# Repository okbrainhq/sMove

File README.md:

# sMove — PCB + three-piece enclosure

> **Schematic ECO 2026-09-15 (SCHEMATIC ONLY — no PCB change, no routing).** Added **SW1**, an off-board pack toggle switch in series in the battery + lead (hard "True OFF", ≥0.5 A / <50 mΩ, wired to the same 2.54 mm wire-pad footprint as J2); routed the charger's open-drain **CHG_N** to **U1 GPIO6** with a 100k pull-up (**R24**); and changed **U4** to **XC6220B331MR-G** (SOT-25, LCSC C86534) with a new footprint `SOT-25_XC6220`. The AP2112K's SOT-23-5 pin map is identical (1=VIN 2=VSS 3=CE 4=NC 5=VOUT), so no rewire was needed. ERC is **0 violations**, matching the pre-change baseline; the board, `dist/` and enclosure data are unchanged and stale until a forward update (F8) plus placement is done. See [Main PCB status](PCB/main/README.md) and [radio/battery architecture](docs/revision-r2/integrated/RADIO-BATTERY.md).

> **Current PCB workspace revision: components staged, UNROUTED.** [Main PCB status](PCB/main/README.md): schematic links repaired; ESP32/U1, USB-C/J1, IMU/U2 and battery +/− holes/J2 remain fixed, with the other 43 footprints staged to the right for manual placement. No tracks/vias; latest zone state preserved. Forward schematic update reports 0 errors/warnings and DRC finds 0 schematic-parity issues. A pre-existing J2/U1 courtyard overlap and unrouted connections remain. **Not for fabrication or charging; exports/enclosure data are stale.**

> **Historical routed PCB revision:** [Routing completion, plane selection and verification](docs/revision-r2/main-routing/README.md): the user's rotated-U8 USB layout is retained, remaining nets use top/bottom routing, In1 is GND and In2 contains power regions. **0 DRC errors, 0 unconnected items, 0 parity issues; one existing J2 library warning.** [Reusable routing/rotation tools](scripts/pcb_tools/README.md) include exact manual coordinates and vias. **Not a fabrication/charging release; `dist/` and enclosure exports remain stale.** Earlier enclosure descriptions below are historical. The prior RED LED GPIO3 change remains required.

> **Previous PCB update:** The [LED is now fully routed on the user's revised layout](docs/revision-r2/led-routing/README.md), with top-left/bottom-right space reserved for future M3 hardware. The enclosure and `PCB/main/dist/` remain older snapshots; their alignment/manufacturing claims below do not apply to the revised PCB without regeneration and review.

**Current review: white rounded Midframe + Top cover + Bottom cover. No screws, nuts, inserts or PCB enclosure-mounting holes. Default outer wall 0.8 mm; configurable and checked at 1.2 mm. No merge, manufacturing release or charging release.**

- [Current enclosure and regeneration](housing/README.md): opposite-side battery/PCB pockets, insulated support, optional PCB adhesive, screwless sleeve/snap covers and an internal perimeter BAT route around the separator edge.
- [PCB](PCB/main/README.md): targeted H1/keepout removal and copper refill; all 1,726 tracks and 97 vias preserved. Circuit, pad geometry, aligned buttons, antenna rules and battery interface unchanged.
- [JLCPCB fabrication/assembly export](scripts/jlcpcb/README.md): regenerates `PCB/main/dist/jlcpcb/` (`gerber.zip`, `bom.csv`, `pick_and_place.csv`, `export-report.json`) from the native KiCad `LCSC`/`MPN` fields on the symbols and footprints.
- [Historical screwless revision evidence](docs/revision-r2/screwless/README.md): fresh configured DRC/ERC, full native comparisons, manifold solids, collision/access checks, actual wall variation, FreeCAD images and hash manifests.
- [Printing/assembly and physical gates](housing/PRINTING-ASSEMBLY.md): actual pack/lead exit, insulation/adhesive, print supports, snap fit/creep, PCB deflection and charging qualification still required. No proven physical fit.

Default envelope including snap reinforcement: **42.85 L × 34.3 W × 19.0 H mm**. Accepted 30×20×3 mm battery candidate / 31×21×4.3 mm complete-pack allowance retained, behind the north antenna exclusion. Main underside faces the body; IMU +Z remains outward. LED, RESET/BOOT and USB-C accesses align to the current native PCB.

Previous [button alignment](docs/revision-r2/button-alignment/README.md), [PCB repair](docs/revision-r2/pcb-repair/README.md), and [two-part case](docs/revision-r2/two-part-case/README.md) records are historical snapshots, not current assembly instructions. Unrelated electronics and history are preserved.

### Enclosure-only RF test prototype

Current `housing/` preserves the validated 25×30 mm PCB unchanged. Three screwless prints integrate a protected original-module antenna cap, source-derived flush USB mouth and internal perimeter BAT route around (not through) the separator. Overall 42.85×34.3×19.0 mm at 0.8 mm walls. See [housing documentation](housing/README.md) for source evidence, nominal checks and physical/RF/sweat qualification holds. No PCB shrinking or external antenna substitution.

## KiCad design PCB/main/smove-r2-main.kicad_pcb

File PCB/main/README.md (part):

# Main PCB — 25 × 30 × 1 mm manual-layout reset

## Current schematic ECO — pack cutoff switch, charger status, 3V3 LDO (2026-09-15, SCHEMATIC ONLY)

Applied to `power.kicad_sch`, `compute.kicad_sch` and `smove-r2-main.kicad_sch`:

* **SW1 — hard pack cutoff.** An off-board toggle switch in series in the battery **+** lead, upstream of the `PACK_P` node. Schematic symbol uses the same 2.54 mm two-pad wire footprint as J2 (`smove-r2-main:BatteryWire_2x_PTH_P2.54mm_D1.0mm`), `in_bom no` (user-supplied off-board part: **≥0.5 A rating, contacts <50 mΩ, ≥6 V DC**). Net split: `/Power/PACK_RAW` = J2.1 + SW1.2, `/Power/PACK_P` = SW1.1 + C2.1 + R14.1 + U6.2 + U6.3. This provides the *True OFF* that `docs/revision-r2/integrated/RADIO-BATTERY.md` records as missing.
* **R24 (100k, LCSC C25741) + `/CHG_N` net — charger status to the MCU.** Charger open-drain `CHG_N` (U6 pin 9) is pulled up to 3V3_MAIN and routed to **U1 pad 20 = GPIO6**; `/CHG_N` = U6.9 + R24.2 + U1.20. New sheet pin added to both the Power and Compute sheet symbols.
* **U4 = XC6220B331MR-G** (Torex, LCSC C86534) replaces `AP2112K-3.3TRG1`. The SOT-25 pin map **1=VIN 2=VSS 3=CE 4=NC 5=VOUT** is the *same function map* as the AP2112K SOT-23-5 it replaces, so no rewire and no pad remap was needed. New footprint `assets/smove-r2-main.pretty/SOT-25_XC6220.kicad_mod` (JEDEC MO-178 Var AA land pattern, identical geometry to `SOT-23-5`); the SW1 symbol was added to `assets/smove-r2-main.kicad_sym`.
* `J2` was moved down 10.16 mm **on the sheet only** (cosmetic, no connectivity change) to make room for SW1.

Verification (KiCad 9.0.8): `kicad-cli sch erc` reports **0 violations — identical to the HEAD baseline**, and `kicad-cli sch export netlist` confirms the three nets above.

**Deliberately not done — no PCB change and no routing.** The board still carries the AP2112K SOT-23-5 at U4 (its footprint field now differs from the schematic) and has no SW1/R24 footprints, so a forward update (F8) plus manual placement is required before parity is restored. `dist/` and the enclosure data remain stale and must be regenerated (`python3 scripts/jlcpcb/export.py PCB/main --overwrite`) after the board is updated. **Engineering prototype — no charge or fabrication approval.**

## Library and asset layout

All project-local KiCad libraries and models now live under `assets/` (moved from the project root; content byte-identical apart from the references below):

| Path | Contents |
|---|---|
| `assets/smove-r2-main.pretty/` | main footprint library (nickname `smove-r2-main`) |
| `assets/imu.pretty/` | integrated-IMU footprint library (nickname `imu`) |
| `assets/smove-r2-main.kicad_sym`, `assets/imu.kicad_sym`, `assets/Device.kicad_sym`, `assets/power.kicad_sym` | project-local symbol libraries |
| `assets/imu-models/` | local STEP models, referenced as `${KIPRJMOD}/assets/imu-models/...` |

`fp-lib-table`/`sym-lib-table` stay at the project root and point at `${KIPRJMOD}/assets/...`. Schematic sheets, project/design-rule files and `dist/` are untouched; only the U2 3D-model path (in the board and in `assets/imu.pretty/InvenSense_QFN-24_3x3mm_P0.4mm.kicad_mod`) changed text.

Verified with KiCad 9.0.8: the board reloads with the same 47 footprints, 461 tracks and 7 zones; DRC reports 0 violations / 0 unconnected / 0 schematic-parity (the DRC library check covers footprint-library resolution), ERC reports 0 violations, and all four symbol libraries parse and still contain every referenced symbol. Historical ECO scripts under `scripts/r2/` (for example `integrated/migrate.py`, `integrated/layout.py`) still name the pre-move project-root paths; they are documented as destructive historical helpers and must not be rerun on this board.

**Status note:** the headings below describe earlier working states. DRC on the currently saved `smove-r2-main.kicad_pcb` reports 0 violations, 0 unconnected items and 0 schematic-parity issues, and no footprint origin lies outside the board outline, so the "UNROUTED / components staged" wording below is stale and has not been rewritten here.

## M3 screw mounting holes with grounded copper rings (2026-09-15)

Three plated 3.2 mm M3 clearance holes were added to the three free board corners, each
with a 5.0 mm grounded copper ring on all four copper layers:

| Ref | Corner | Centre (native mm) | Hole | Ring | Net |
|---|---|---|---|---|---|
| **H1** | top-left | 103.20, 103.20 | 3.2 mm plated | 5.0 mm Ø, 0.90 mm annular, mask open | `GND` |
| **H2** | bottom-left | 103.20, 126.80 | 3.2 mm plated | same | `GND` |
| **H3** | bottom-right | 121.80, 126.80 | 3.2 mm plated | same | `GND` |

* Each centre is exactly 3.20 mm in from both adjacent edges, so the three holes are
  identical except for the corner they avoid. The top-right corner is **occupied** by J2
  and R3/R4/U8 — 1.4 mm of clear width, less than the drill.
* Footprint `smove-r2-main:MountingHole_3.2mm_M3_Pad_5mm` lives in
  `assets/smove-r2-main.pretty/`. It is a reduced-ring variant of KiCad's
  `MountingHole:MountingHole_3.2mm_M3_Pad`: that part's 6.4 mm pad needs 3.45 mm of
  board-edge clearance and does not fit any corner of this board. 5.0 mm is the largest
  ring that keeps ≥0.25 mm copper-to-edge (actual 0.70 mm), ≥0.15 mm foreign-net
  clearance (actual 0.44/1.10/0.81 mm) and a non-overlapping courtyard (actual
  0.26/0.41/0.33 mm, courtyard = the 5.5 mm M3 head envelope) at all three positions.
* `board_only`, excluded from BOM and position files, no schematic symbol: mounting
  hardware is not a purchased or placed part, and schematic parity stays 0.
* **Zones were deliberately not refilled.** The rings join the GND node by overlapping
  the saved In1.Cu plane (all three centres are inside the fill, DRC 0 unconnected). A
  fresh refill would re-cut 31.6 mm² of that plane even on the unmodified board, which
  is not part of this change.
* Board diff is **+333 lines, 0 deletions**; deleting the three footprint blocks
  reproduces the previous board byte-for-byte. `bom.csv` and `pick_and_place.csv` are
  byte-identical; the Gerbers gain only the three 5.0 mm rings and their mask openings,
  and the PTH drill gains one `T4C3.200` tool with three hits.
* DRC **0 / 0 / 0**, ERC **0**. See the
  [change record](../../docs/revision-r2/m3-mounting-holes/README.md) and its
  `verification.json`; reproduce with `python3 scripts/r2/final/m3_mounting_holes.py
  --check --geometry` and `python3 scripts/r2/m3-mounting-holes/verify.py`.
* **The enclosure does not have these holes.** `housing/` is still the screwless
  revision (no bosses, threads or inserts); it needs a companion revision before M3
  hardware is usable. Physical fit, torque and the RF effect of the new metal near the
  ESP32-C3 antenna are unqualified.

## Silkscreen outlines, pin-1 markers and free-library parts (2026-09-15)

All 46 assembled parts still carry verified `LCSC`+`MPN` fields, and the export
(`python3 scripts/jlcpcb/export.py PCB/main`) now also reflects these changes; see the
[change record](../../docs/revision-r2/silk-and-basic-parts/README.md) and its
`verification.json`, renders and live BOM audit.

* **U6** (BQ24074RGTR) had *no* silkscreen, so it had no pin-1 indicator: three corner
  brackets plus the same outside pin-1 arrowhead the IMU (U2) uses now point at the
  TS/pad-1 corner.
* **U1** (ESP32-C3-MINI-1) body outline and antenna boundary existed only on `F.Fab`.
  `F.Fab` is not part of the Gerber set, so JLCPCB's placement preview showed the module
  as bare 0.4 mm pads — that is why it "did not line up" there. The body outline is now
  copied to `F.SilkS`, clipped at the 100.0 mm board edge where the module overhangs,
  and the `F.Fab` corner chamfer is deliberately not copied (it crosses the left anchor pad).
* **J1** (USB-C receptacle) had no silkscreen at all — the standard shell lines were on
  `F.Fab` — so the same problem applied. Its shell sides and pad-side end are now on
  `F.SilkS`, offset past the `S1` shell pads and clipped at the board-edge notch.
* **D1** (LTST-C19HE1WT) got a closed silkscreen outline outside the land pattern with a
  gap over the pad-1 corner.
* The same geometry was added to the project-local library footprints
  (`assets/smove-r2-main.pretty/*.kicad_mod`), so the DRC library check stays clean.
* **C3** moved from `C29277` (22 µF 10 V, Extended, $3 setup fee) to **`C45783`
  (22 µF 25 V X5R 0805, Basic)**. Every other resistor and capacitor is already
  Basic/Preferred Extended and therefore fee-free, including R21 (`C25924`); the
  estimated extended-part fee drops from $33.00 to $30.00, and the remaining charge is
  the ten design-fixed actives.

Verification: DRC **0 violations / 0 unconnected / 0 schematic-parity**, ERC **0**, added
silk keeps ≥0.17 mm to the nearest pad (board rule 0.10 mm), `F_Silkscreen.gto` gains 36
draw commands, `bom.csv` differs only in the C3 row and `pick_and_place.csv` is
byte-identical. C45783's pocket-height check and a fresh DC-bias screen are still open.

## JLCPCB fabrication and assembly export

`/usr/bin/python3 scripts/jlcpcb/export.py PCB/main` (add `--overwrite` to refresh an existing
set) writes `dist/jlcpcb/`: `gerber.zip` (all four copper layers, masks, silkscreen, paste, edge
cuts, separate PTH/NPTH millimetre drills), `bom.csv`, `pick_and_place.csv` and
`export-report.json`. See the [export tool documentation](../../scripts/jlcpcb/README.md).

- Generated from the currently saved board (47 footprints, 461 tracks, 70 vias, 7 zones, 4 copper
  layers, aux origin 100/135) at this revision. Native DRC/parity on that same file reports
  **0 violations, 0 unconnected items, 0 schematic-parity issues**; the export tool re-verifies
  KiCad's own position output against the board file before writing anything.
- All **46** assembled parts carry a JLCPCB/LCSC catalogue number in the native `LCSC` field,
  together with `MPN`, on both the schematic symbols and the board footprints. The verified
  numbers are recorded in [main-parts.csv](../../docs/revision-r2/main-parts.csv) and
  [stock.json](../../docs/revision-r2/stock.json). J2 (the two plated battery wire holes) is
  intentionally PCB-only and excluded from both BOM and CPL.
- Engineering export only: **not a fabrication, assembly or charging release**. The tool does not
  refill zones, run DRC/ERC, check supplier stock or qualify any purchase code, and `housing/`
  remains a separate historical snapshot.

## Current: schematic links repaired; components staged — UNROUTED

**All 47 schematic footprints are now present.** U1 (ESP32), J1 (USB-C), U2 (IMU), and J2 (battery +/− holes) retain their poses and geometry. The other **43 footprints are staged outside the board to the right** for manual placement. No tracks or vias were added.

The reported dialog was **Update Schematic from PCB**, the reverse direction. Use **Tools → Update PCB from Schematic (F8)** to bring schematic components into the board. The four old footprint paths also contained an extra root-sheet UUID; one reference-based re-link repaired them without replacing or moving the footprints. Re-link is now off for normal updates. A repeat forward-update preview reports **0 errors and 0 warnings**, without duplicate additions. KiCad also repaired duplicate pad UUIDs on save; all pad geometry/nets and footprint UUIDs remain unchanged.

[Update verification](../../docs/revision-r2/manual-layout-reset/schematic-update-verification.json): **0 schematic-parity issues**, 148 expected unconnected items, and one **pre-existing J2/U1 courtyard overlap**, left unchanged to preserve both fixed positions. Schematics and design rules on disk are unchanged. The latest saved zone state was preserved: five rule areas and one filled In1 GND plane; the earlier six-unfilled-zone reset below is historical. **Not for manufacture or charging; exports remain stale.**

## Historical: manual placement/routing reset — UNROUTED

Only **U1 (ESP32), J1 (USB-C), U2 (IMU), and J2 (battery +/− through-hole pads)** remain in the PCB layout, with their complete footprint definitions, positions, orientations and pad/net assignments unchanged. The other **43 footprints were deleted from the PCB only**; all schematic sheets and project/rule files remain unchanged.

Removed **500 track segments, 124 vias, and all 38 cached copper-fill polygons**. All six copper-zone definitions are retained **unfilled**, including In1 GND and the In2 GND / 3V3_MAIN / PACK_P regions. Board outline, stackup, drawings and all keepouts are unchanged. This is actual copper removal, not merely hidden pours.

[Verification](../../docs/revision-r2/manual-layout-reset/verification.json): exact-token preservation check and native board load pass; native DRC reports **0 geometric violations**, **45 intentionally unconnected items**, and **43 expected missing-footprint parity warnings**, plus the existing J2 library-footprint mismatch warning. Previous routed-board acceptance scripts/reports below are historical and are not acceptance criteria for this reset. **Not for fabrication/assembly/charging; existing exports and enclosure placement data are stale.**

For manual placement, open `smove-r2-main.kicad_pro` in KiCad and use **Update PCB from Schematic (F8)** when ready to re-add the missing footprints. Do not delete their schematic symbols. The standalone PCB Editor has this command disabled; launch the editors through the project. J2 was restored verbatim from the pre-reset board at the user’s request, retaining both battery +/− holes. The other 43 missing components have not been re-added or parked outside the board.

## Historical: routed review candidate

See the [routing completion and plane-selection evidence](../../docs/revision-r2/main-routing/README.md). The user's rotated-U8 USB routing is preserved, remaining nets are connected on **F.Cu/B.Cu**, In1 is continuous GND, and In2 has bounded **3V3_MAIN / PACK_P power regions** with GND elsewhere. C7 alone is rotated 180° to fix its isolated ground connection; other placements, pad nets and keepouts are unchanged.

**Fresh native checks: 0 DRC errors, 0 unconnected items, 0 schematic-parity issues, 0 ERC violations; one existing J2 footprint-library warning.** Reusable coordinate routing, via placement, rotation previews, explicit rip-up and cleanup tools are documented in [scripts/pcb_tools](../../scripts/pcb_tools/README.md). Run `/usr/bin/python3 scripts/r2/main-routing/verify.py` for current acceptance checks.

**Not released for fabrication or charging.** USB impedance, current/thermal margins and return paths still need engineering review. Some low-speed paths take long perimeter detours. `dist/` and the enclosure are stale; no manufacturing exports were regenerated.

## Historical: grouped placement review — UNROUTED

See the [placement revision and researched routing strategy](../../docs/revision-r2/placement-routing/README.md). U1, USB, battery pads, outline and both M3 reserved positions are unchanged. The LED/buttons are upper-left, charger/regulator parts are together beside USB, and U2 remains at X112.5 with its original orientation, now at Y126.5. RED is reassigned from GPIO6 to GPIO3; GREEN=GPIO7 and BLUE=GPIO10 remain unchanged. Firmware must adopt the RED pin change.

**Placement only: 152 unconnected items; zero tracks/vias.** Obsolete routing was removed deliberately, not left connecting the wrong pads. Current zone definitions are retained but unfilled; the researched power-region strategy is not implemented yet. Placement geometry, ERC and schematic parity pass, with the existing J2 library-footprint warning. This is **not a finished reroute or manufacturing/charging release**. Existing `dist/` and enclosure openings are stale.

Run `/usr/bin/python3 scripts/r2/placement-routing/review.py` for this revision's checks. Do not use the historical LED-only verifier or layout generators as current acceptance tests.

## Historical: LED routed on the previous layout

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
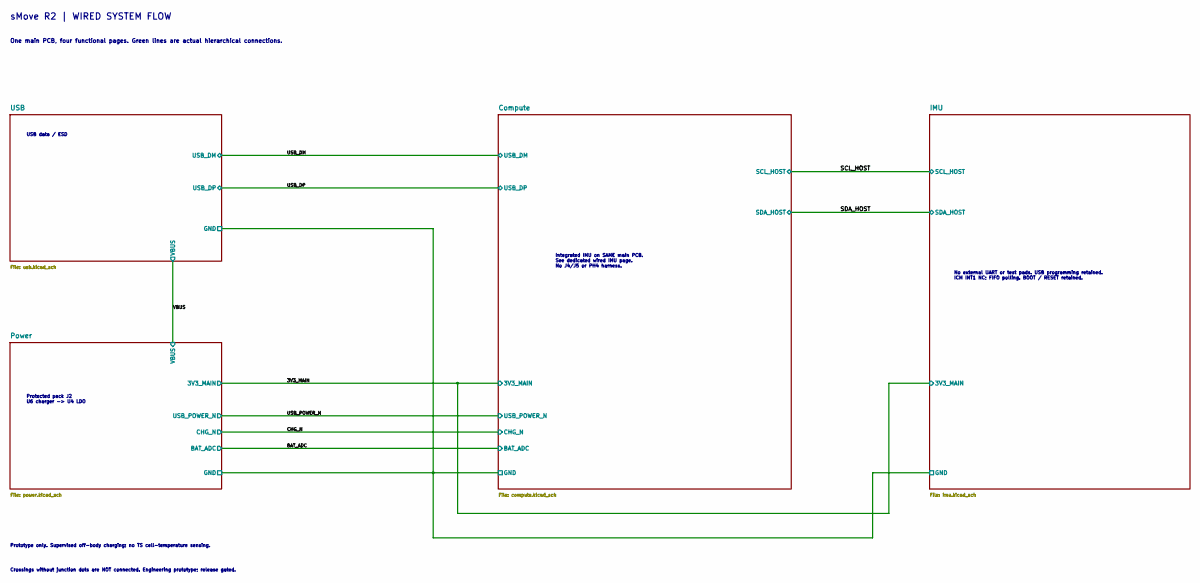
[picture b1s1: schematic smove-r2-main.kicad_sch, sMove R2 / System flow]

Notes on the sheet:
sMove R2 | WIRED SYSTEM FLOW
One main PCB, four functional pages. Green lines are actual hierarchical connections.
USB data / ESD
Protected pack J2 U6 charger -> U4 LDO
Integrated IMU on SAME main PCB. See dedicated wired IMU page. No J4/J5 or PH4 harness.
Prototype only. Supervised off-body charging; no TS cell-temperature sensing.
Crossings without junction dots are NOT connected. Engineering prototype; release gated.
No external UART or test pads. USB programming retained. ICM INT1 NC; FIFO polling. BOOT / RESET retained.

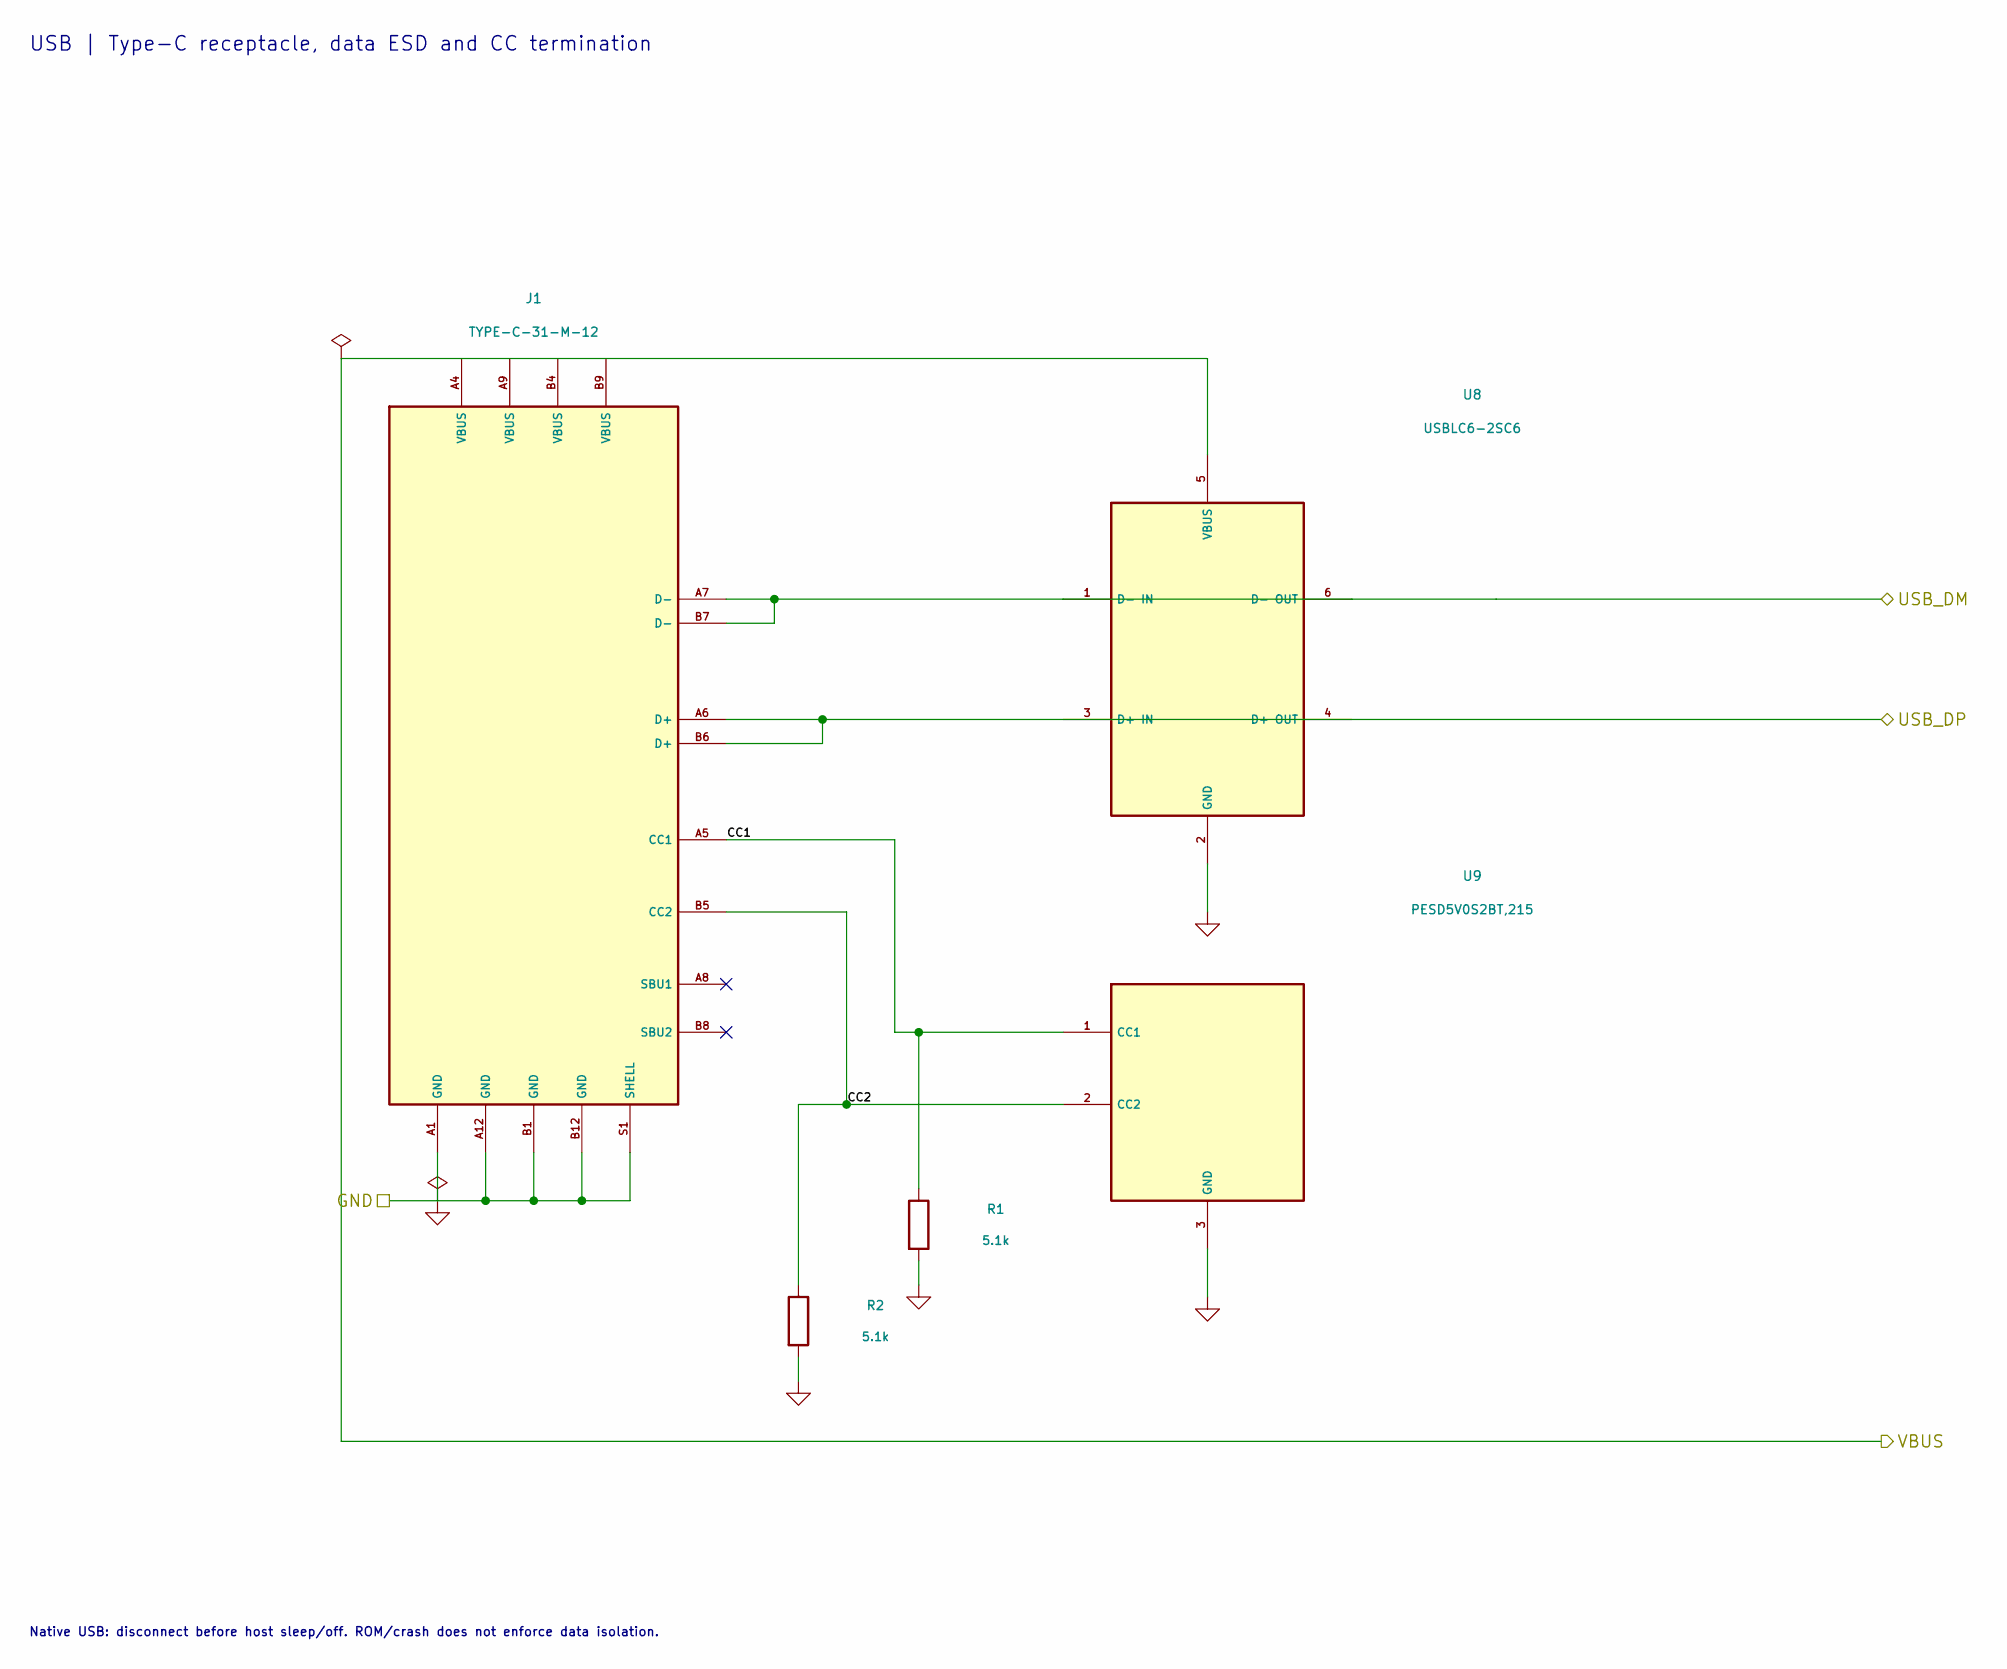
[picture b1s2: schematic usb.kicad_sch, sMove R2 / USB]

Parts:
J1: TYPE-C-31-M-12; USB_C_Receptacle_HRO_TYPE-C-31-M-12; MPN TYPE-C-31-M-12; LCSC C165948
R1, R2: 5.1k; R_0402_1005Metric; MPN 0402WGF5101TCE; LCSC C25905
U8: USBLC6-2SC6; SOT-23-6; MPN USBLC6-2SC6; LCSC C7519
U9: PESD5V0S2BT,215; SOT-23; MPN PESD5V0S2BT,215; LCSC C49338

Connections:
/USB/CC1: J1.A5 (CC1), R1.1, U9.1 (CC1)
/USB/CC2: J1.B5 (CC2), R2.1, U9.2 (CC2)
/USB_DM: J1.A7 (D-), J1.B7 (D-), U8.1 (D-_IN), U8.6 (D-_OUT); also elsewhere on the board
/USB_DP: J1.A6 (D+), J1.B6 (D+), U8.3 (D+_IN), U8.4 (D+_OUT); also elsewhere on the board
/VBUS: J1.A4 (VBUS), J1.A9 (VBUS), J1.B4 (VBUS), J1.B9 (VBUS), U8.5 (VBUS); also elsewhere on the board
GND: J1.A1 (GND), J1.A12 (GND), J1.B1 (GND), J1.B12 (GND), J1.S1 (SHELL), R1.2, R2.2, U8.2 (GND), U9.3 (GND); also elsewhere on the board

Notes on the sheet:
Native USB: disconnect before host sleep/off. ROM/crash does not enforce data isolation.
USB | Type-C receptacle, data ESD and CC termination

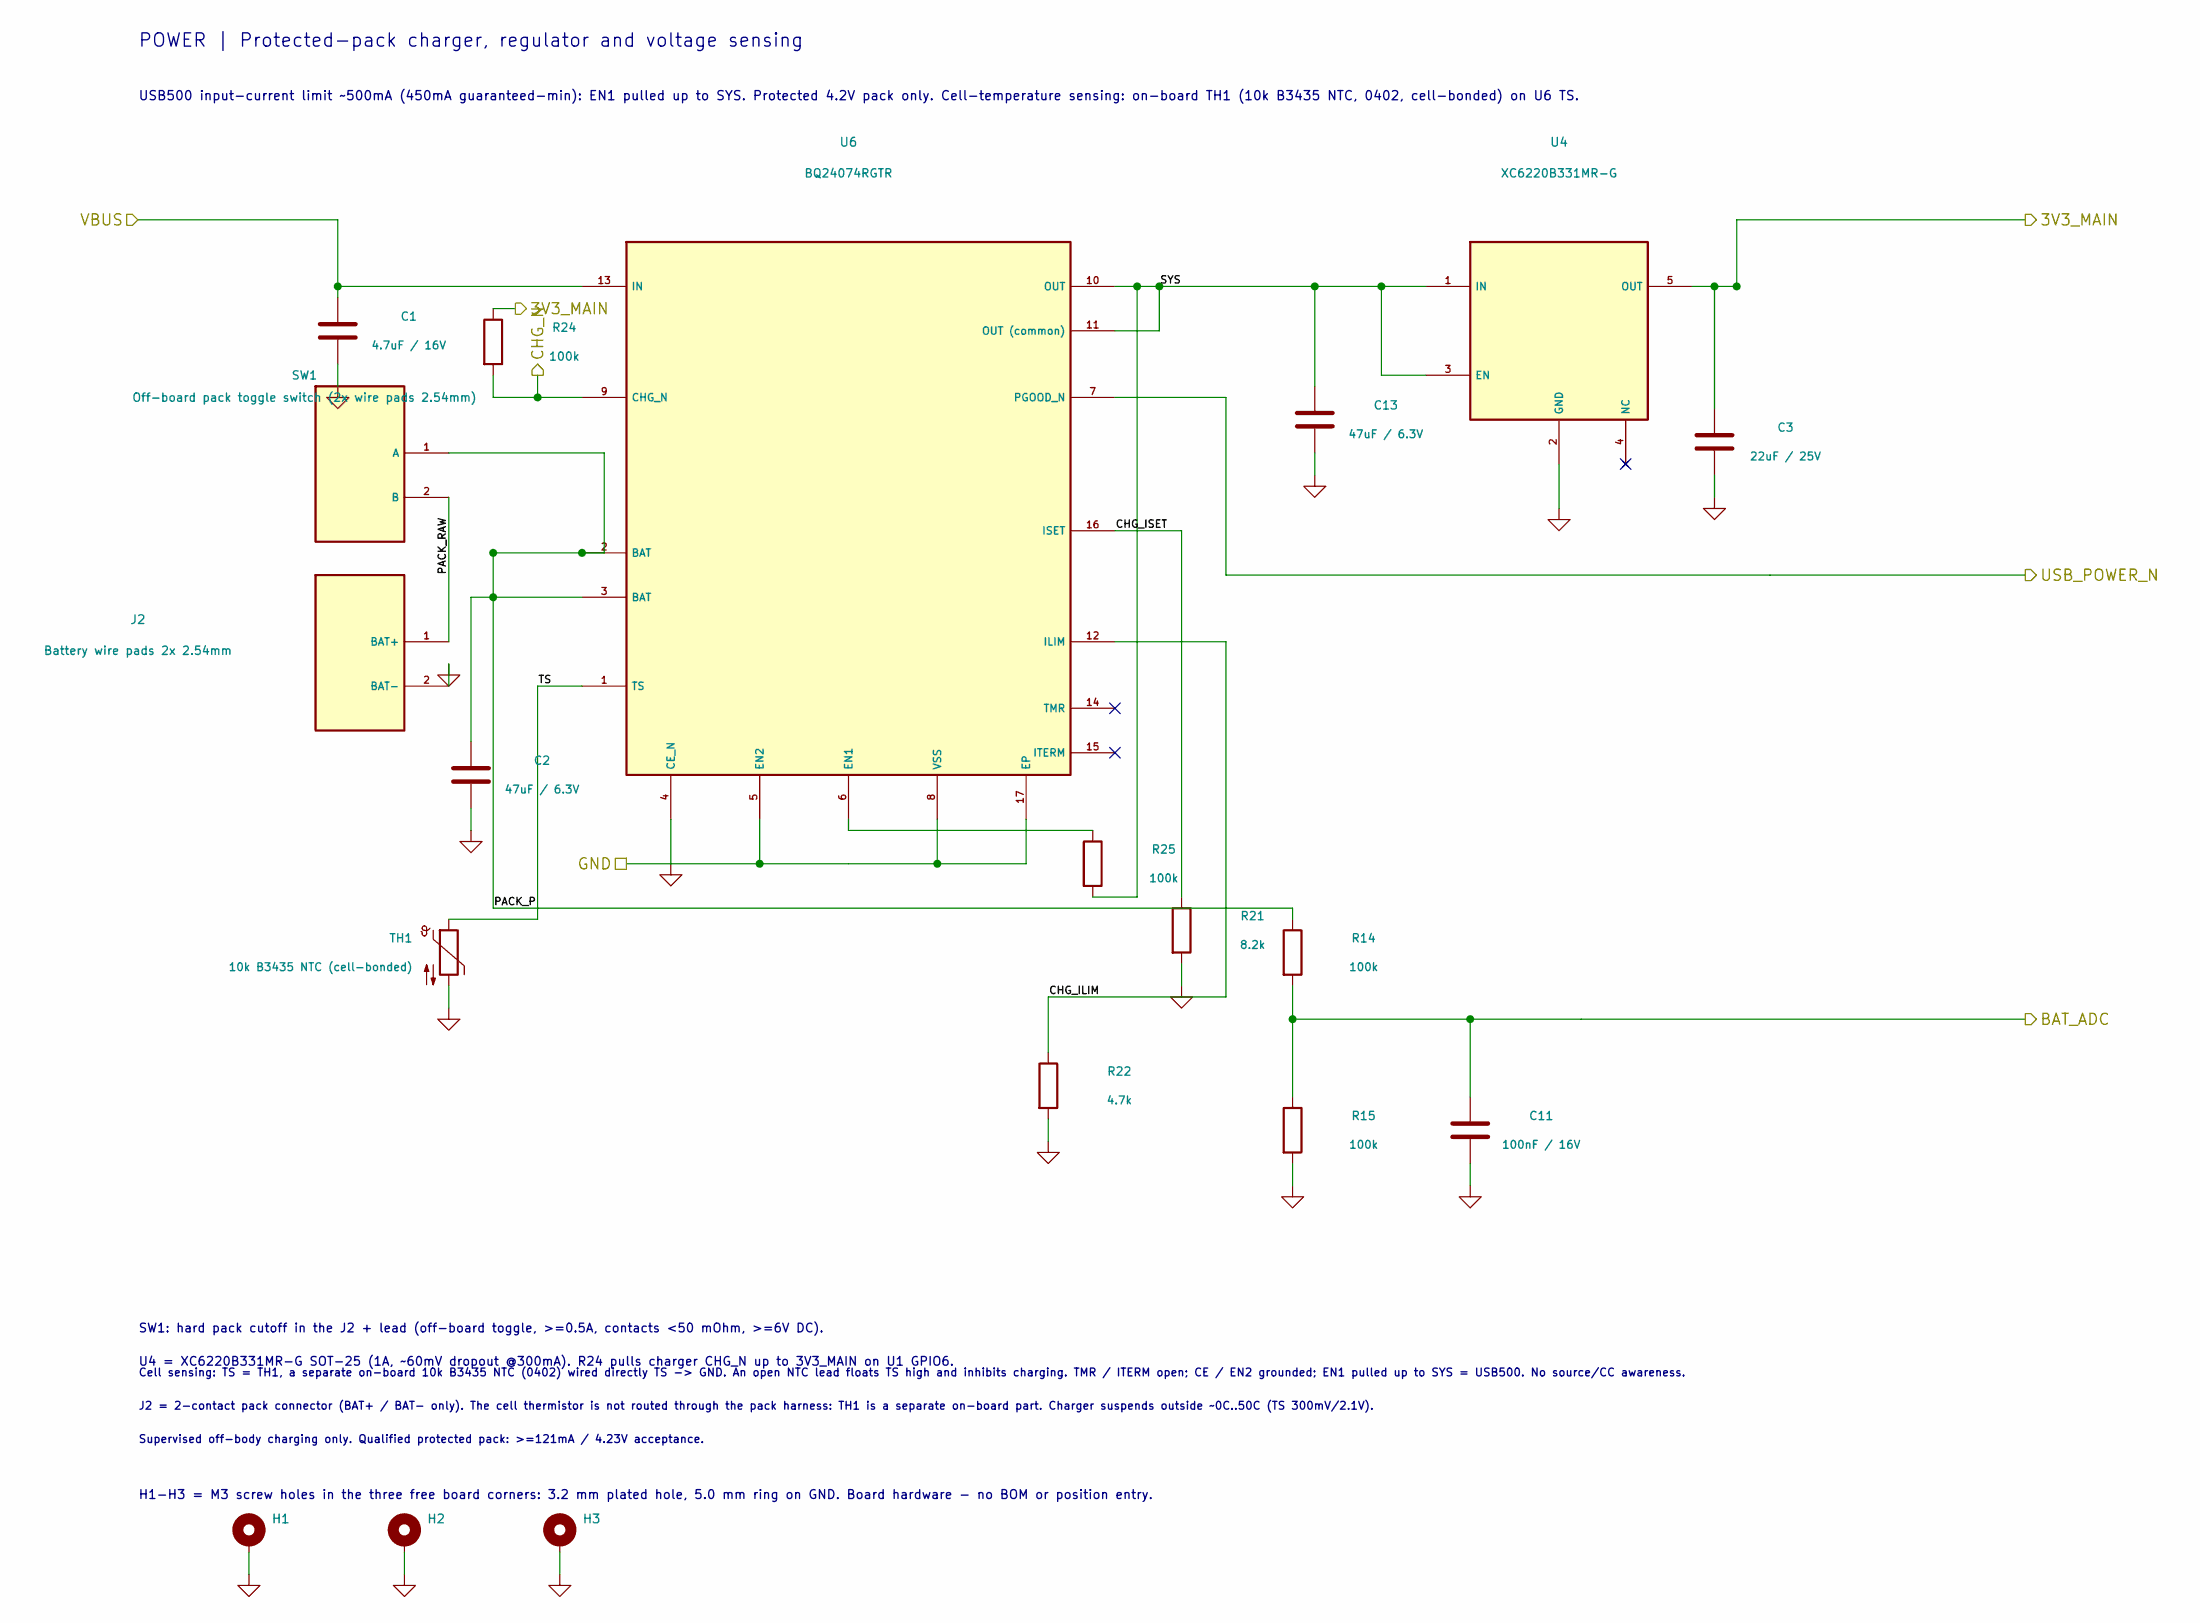
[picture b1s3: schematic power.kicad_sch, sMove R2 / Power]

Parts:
C1: 4.7uF / 16V; C_0603_1608Metric; MPN CL10A475KO8NNNC; LCSC C19666
C2, C13: 47uF / 6.3V; C_0805_2012Metric; MPN CL21A476MQYNNNE; LCSC C16780
C3: 22uF / 25V; C_0805_2012Metric; MPN CL21A226MAQNNNE; LCSC C45783
C11: 100nF / 16V; C_0402_1005Metric; MPN CL05B104KO5NNNC; LCSC C1525
H1, H2, H3: MountingHole_3.2mm_M3_Pad_5mm
J2: Battery wire pads 2x 2.54mm; BatteryWire_2x_PTH_P2.54mm_D1.0mm
R14, R15, R24, R25: 100k; R_0402_1005Metric; MPN 0402WGF1003TCE; LCSC C25741
R21: 8.2k; R_0402_1005Metric; MPN 0402WGF8201TCE; LCSC C25924
R22: 4.7k; R_0402_1005Metric; MPN 0402WGF4701TCE; LCSC C25900
SW1: Off-board pack toggle switch (2x wire pads 2.54mm); BatteryWire_2x_PTH_P2.54mm_D1.0mm
TH1: 10k B3435 NTC (cell-bonded); NTC_0402_1005Metric; MPN NTCG103JF103FT1; LCSC C209959
U4: XC6220B331MR-G; SOT-25_XC6220; MPN XC6220B331MR-G; LCSC C86534
U6: BQ24074RGTR; BQ24074_RGT; MPN BQ24074RGTR; LCSC C54313

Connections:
/3V3_MAIN: C3.1, R24.1, U4.5 (OUT); also elsewhere on the board
/BAT_ADC: C11.1, R14.2, R15.1; also elsewhere on the board
/CHG_N: R24.2, U6.9 (CHG_N); also elsewhere on the board
/Power/CHG_ILIM: R22.1, U6.12 (ILIM)
/Power/CHG_ISET: R21.1, U6.16 (ISET)
/Power/PACK_P: C2.1, R14.1, SW1.1 (A), U6.2 (BAT), U6.3 (BAT)
/Power/PACK_RAW: J2.1 (BAT+), SW1.2 (B)
/Power/SYS: C13.1, R25.2, U4.1 (IN), U4.3 (EN), U6.10 (OUT), U6.11 (OUT_(common))
/Power/TS: TH1.1, U6.1 (TS)
/USB_POWER_N: U6.7 (PGOOD_N); also elsewhere on the board
/VBUS: C1.1, U6.13 (IN); also elsewhere on the board
GND: C1.2, C2.2, C3.2, C11.2, C13.2, H1.1, H2.1, H3.1, J2.2 (BAT-), R15.2, R21.2, R22.2, TH1.2, U4.2 (GND), U6.4 (CE_N), U6.5 (EN2), U6.8 (VSS), U6.17 (EP); also elsewhere on the board
unnamed: R25.1, U6.6 (EN1)

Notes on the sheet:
USB500 input-current limit ~500mA (450mA guaranteed-min): EN1 pulled up to SYS. Protected 4.2V pack only. Cell-temperature sensing: on-board TH1 (10k B3435 NTC, 0402, cell-bonded) on U6 TS.
Cell sensing: TS = TH1, a separate on-board 10k B3435 NTC (0402) wired directly TS -> GND. An open NTC lead floats TS high and inhibits charging. TMR / ITERM open; CE / EN2 grounded; EN1 pulled up to SYS = USB500. No source/CC awareness.
J2 = 2-contact pack connector (BAT+ / BAT- only). The cell thermistor is not routed through the pack harness: TH1 is a separate on-board part. Charger suspends outside ~0C..50C (TS 300mV/2.1V).
Supervised off-body charging only. Qualified protected pack: >=121mA / 4.23V acceptance.
POWER | Protected-pack charger, regulator and voltage sensing
SW1: hard pack cutoff in the J2 + lead (off-board toggle, >=0.5A, contacts <50 mOhm, >=6V DC).
U4 = XC6220B331MR-G SOT-25 (1A, ~60mV dropout @300mA). R24 pulls charger CHG_N up to 3V3_MAIN on U1 GPIO6.
H1-H3 = M3 screw holes in the three free board corners: 3.2 mm plated hole, 5.0 mm ring on GND. Board hardware - no BOM or position entry.

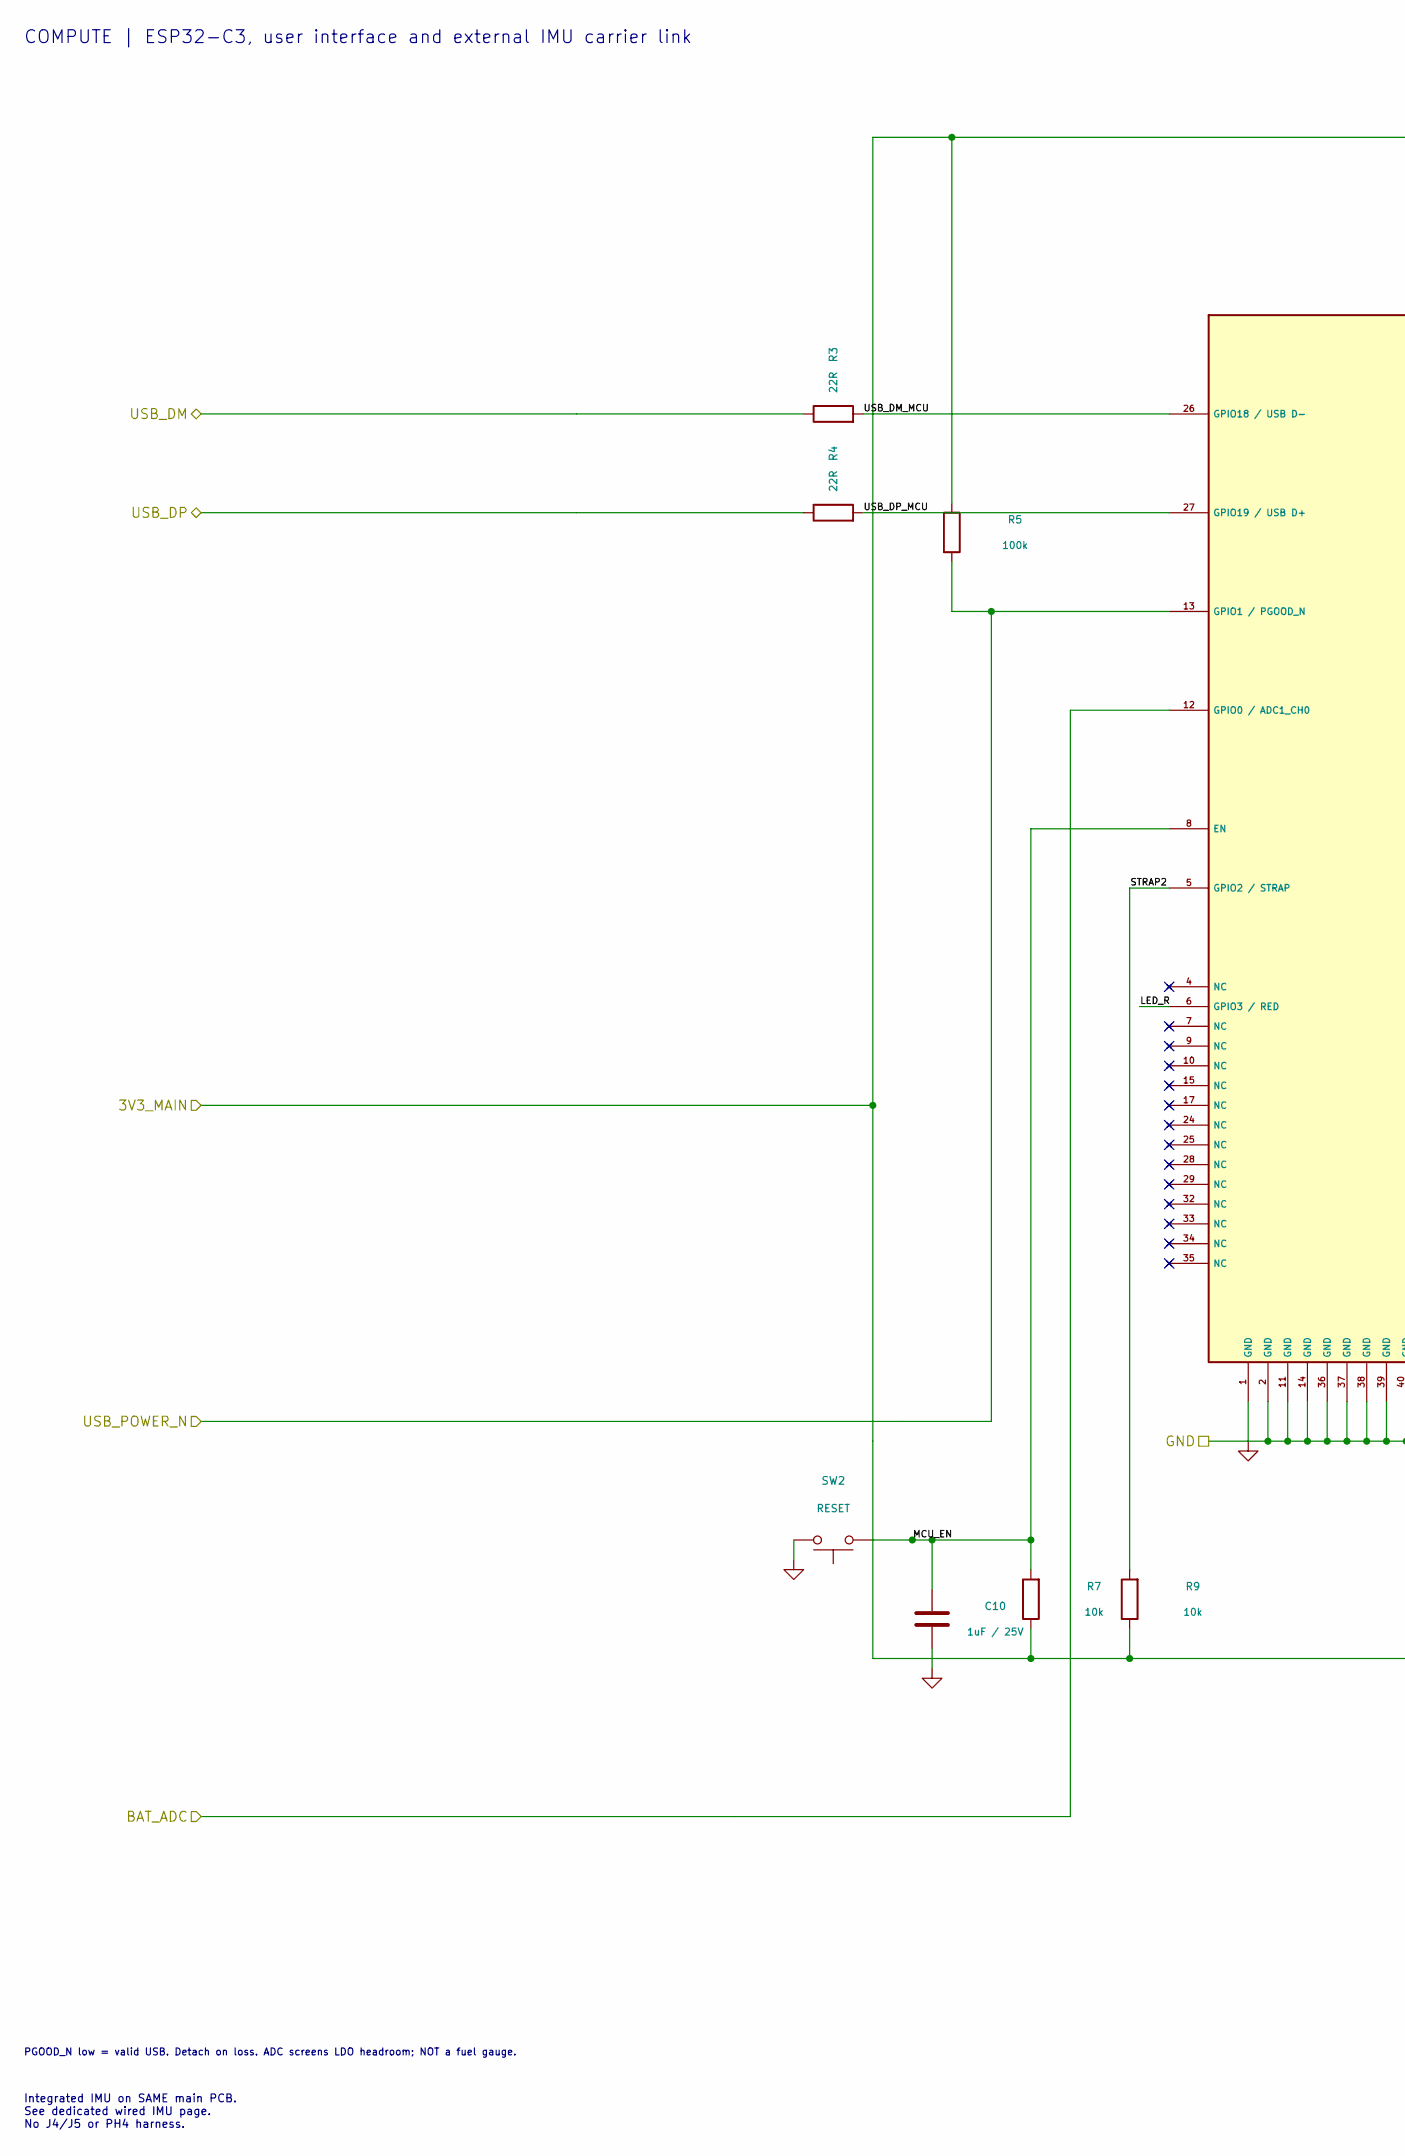
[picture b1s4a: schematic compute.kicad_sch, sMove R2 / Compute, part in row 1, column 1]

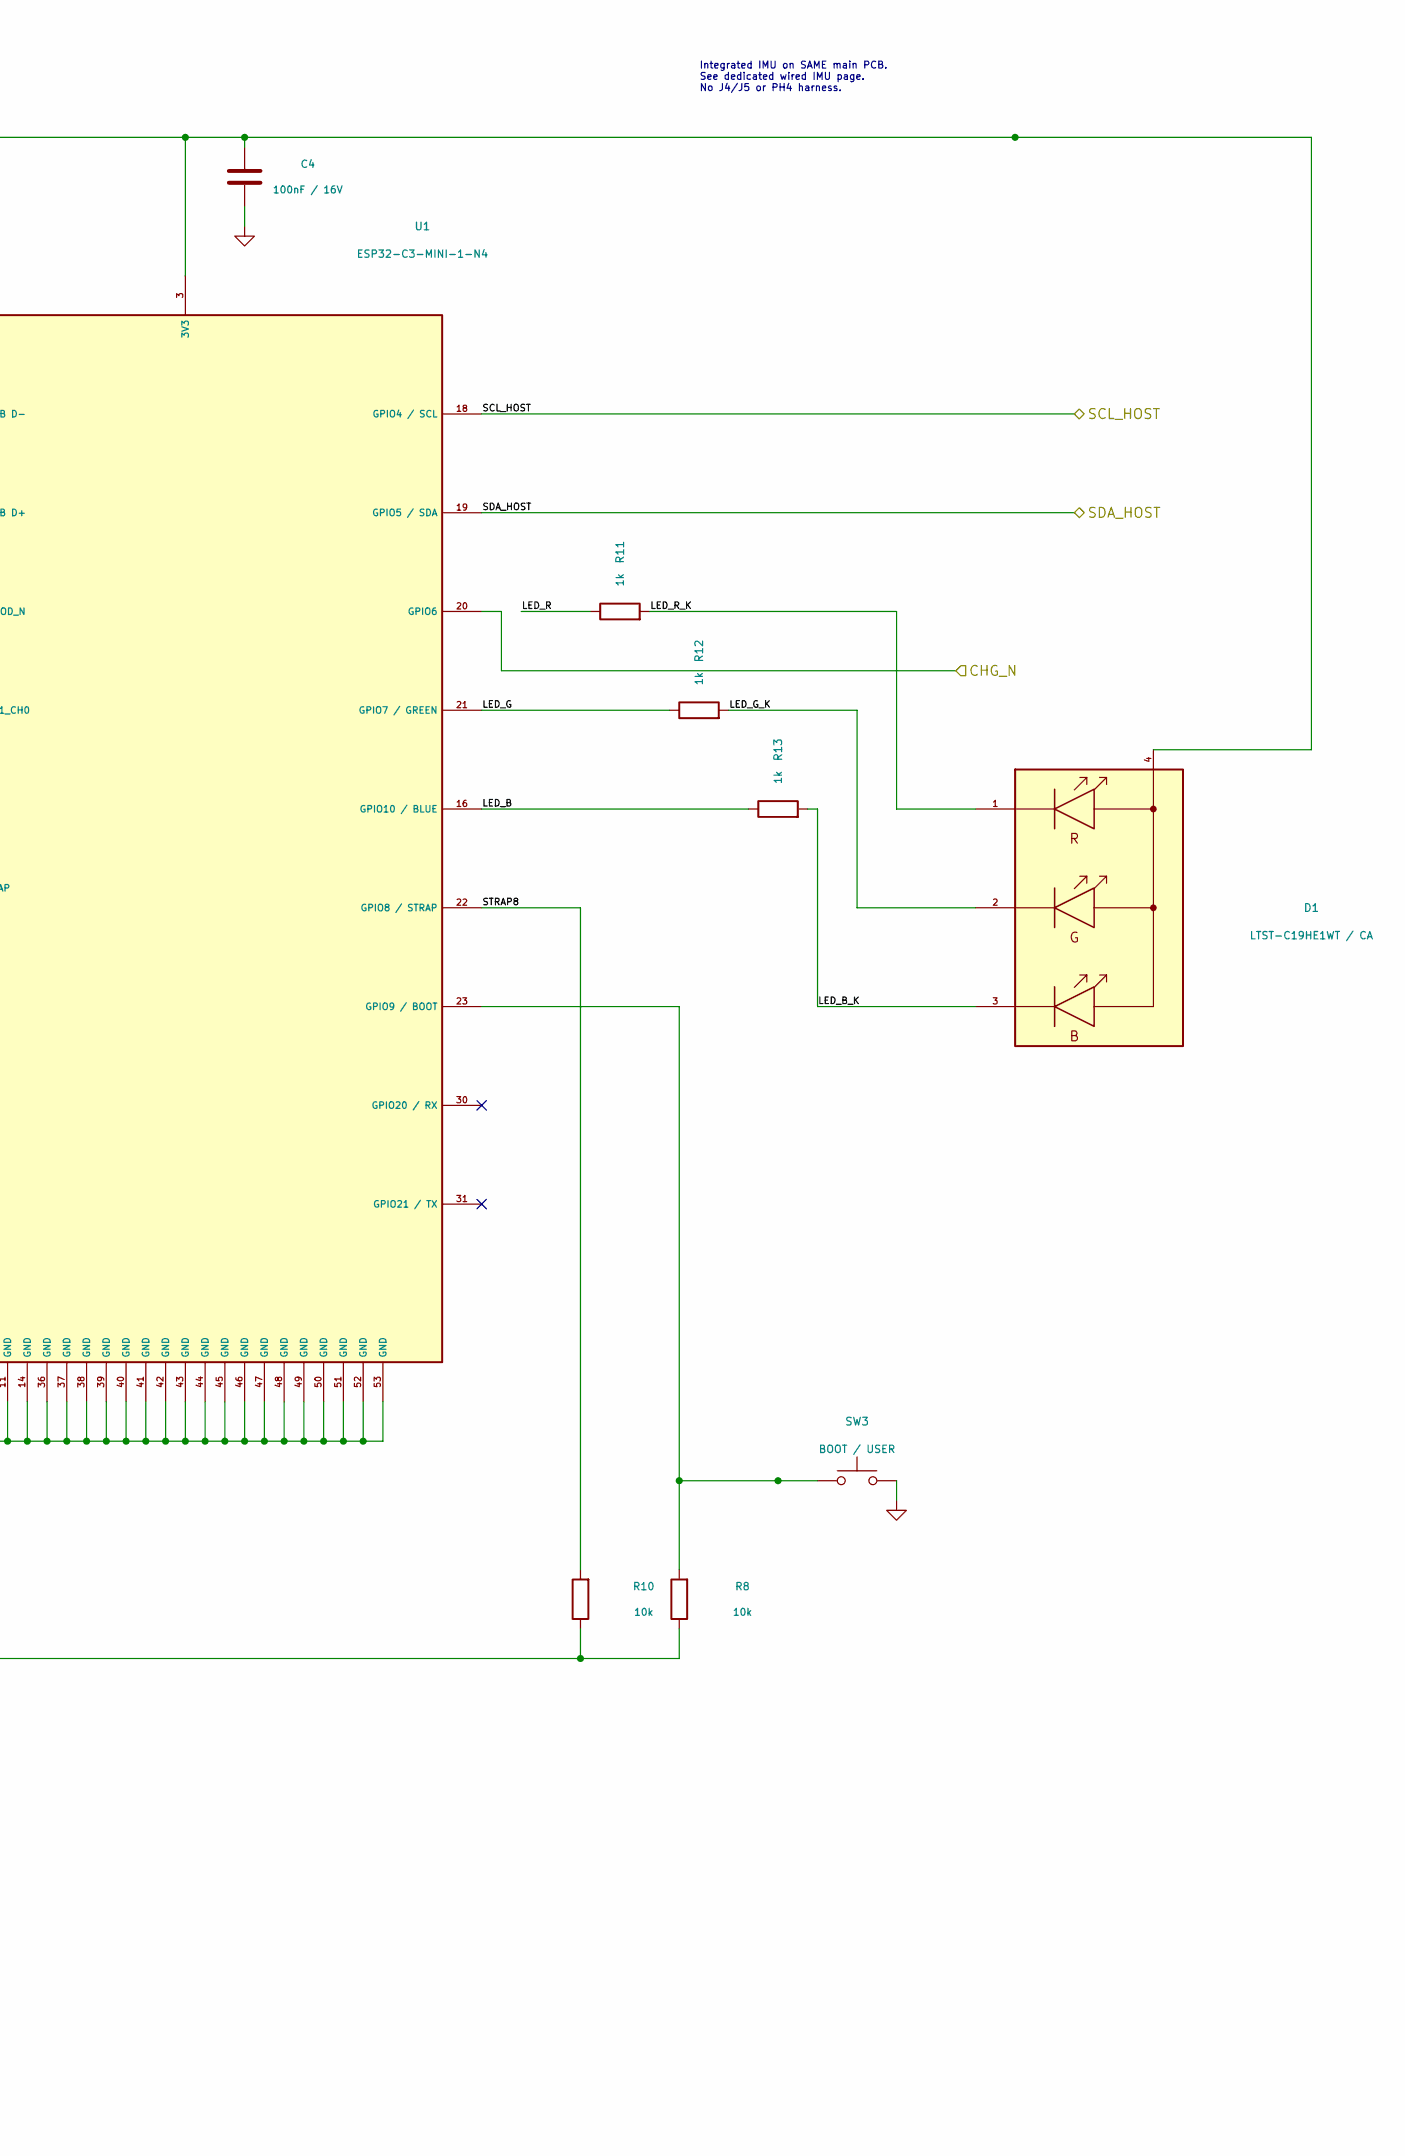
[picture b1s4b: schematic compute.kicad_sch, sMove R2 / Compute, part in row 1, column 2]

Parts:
C4: 100nF / 16V; C_0402_1005Metric; MPN CL05B104KO5NNNC; LCSC C1525
C10: 1uF / 25V; C_0402_1005Metric; MPN CL05A105KA5NQNC; LCSC C52923
D1: LTST-C19HE1WT / CA; LED_LiteOn_LTST-C19HE1WT; MPN LTST-C19HE1WT; LCSC C458749
R3, R4: 22R; R_0402_1005Metric; MPN 0402WGF220JTCE; LCSC C25092
R5: 100k; R_0402_1005Metric; MPN 0402WGF1003TCE; LCSC C25741
R7, R8, R9, R10: 10k; R_0402_1005Metric; MPN 0402WGF1002TCE; LCSC C25744
R11, R12, R13: 1k; R_0402_1005Metric; MPN 0402WGF1001TCE; LCSC C11702
SW2: RESET; TS1088; MPN TS-1088-AR02016; LCSC C720477
SW3: BOOT / USER; TS1088; MPN TS-1088-AR02016; LCSC C720477
U1: ESP32-C3-MINI-1-N4; ESP32-C3-MINI-1; MPN ESP32-C3-MINI-1-N4; LCSC C2838502

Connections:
/3V3_MAIN: C4.1, D1.4 (A), R5.1, R7.1, R8.1, R9.1, R10.1, U1.3 (3V3); also elsewhere on the board
/BAT_ADC: U1.12 (GPIO0_/_ADC1_CH0); also elsewhere on the board
/CHG_N: U1.20 (GPIO6); also elsewhere on the board
/Compute/LED_B: R13.1, U1.16 (GPIO10_/_BLUE)
/Compute/LED_B_K: D1.3 (B_K), R13.2
/Compute/LED_G: R12.1, U1.21 (GPIO7_/_GREEN)
/Compute/LED_G_K: D1.2 (G_K), R12.2
/Compute/LED_R: R11.1, U1.6 (GPIO3_/_RED)
/Compute/LED_R_K: D1.1 (R_K), R11.2
/Compute/MCU_EN: C10.1, R7.2, SW2.1, U1.8 (EN)
/Compute/STRAP2: R9.2, U1.5 (GPIO2_/_STRAP)
/Compute/STRAP8: R10.2, U1.22 (GPIO8_/_STRAP)
/Compute/USB_DM_MCU: R3.2, U1.26 (GPIO18_/_USB_D-)
/Compute/USB_DP_MCU: R4.2, U1.27 (GPIO19_/_USB_D+)
/SCL_HOST: U1.18 (GPIO4_/_SCL); also elsewhere on the board
/SDA_HOST: U1.19 (GPIO5_/_SDA); also elsewhere on the board
/USB_DM: R3.1; also elsewhere on the board
/USB_DP: R4.1; also elsewhere on the board
/USB_POWER_N: R5.2, U1.13 (GPIO1_/_PGOOD_N); also elsewhere on the board
GND: C4.2, C10.2, SW2.2, SW3.2, U1.1 (GND), U1.2 (GND), U1.11 (GND), U1.14 (GND), U1.36 (GND), U1.37 (GND), U1.38 (GND), U1.39 (GND), U1.40 (GND), U1.41 (GND), U1.42 (GND), U1.43 (GND), U1.44 (GND), U1.45 (GND), U1.46 (GND), U1.47 (GND), U1.48 (GND), U1.49 (GND), U1.50 (GND), U1.51 (GND), U1.52 (GND), U1.53 (GND); also elsewhere on the board
unnamed: R8.2, SW3.1, U1.23 (GPIO9_/_BOOT)

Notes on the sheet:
COMPUTE | ESP32-C3, user interface and external IMU carrier link
PGOOD_N low = valid USB. Detach on loss. ADC screens LDO headroom; NOT a fuel gauge.
Integrated IMU on SAME main PCB. See dedicated wired IMU page. No J4/J5 or PH4 harness.
